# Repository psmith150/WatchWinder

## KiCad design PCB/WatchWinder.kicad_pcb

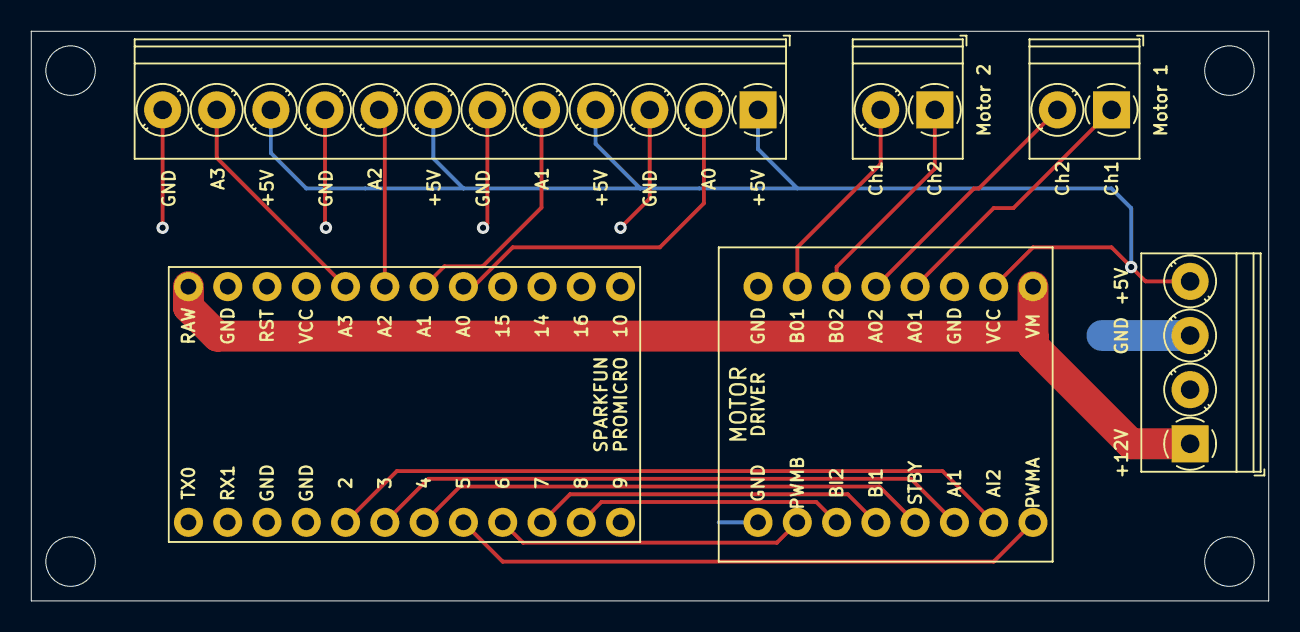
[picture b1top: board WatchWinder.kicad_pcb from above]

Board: 2 copper layers, 80.0 x 36.8 mm, 6 parts (0 on the bottom side), 18 nets.

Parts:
B1: SPARKFUN; SPARKFUN_PRO_MICRO
J1, J2: Screw_Terminal_01x02; TerminalBlock_Phoenix_PT-1,5-2-3.5-H_1x02_P3.50mm_Horizontal
J3: Screw_Terminal_01x12; TerminalBlock_Phoenix_PT-1,5-12-3.5-H_1x12_P3.50mm_Horizont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
J4: MOTOR; DRIVER
J5: Screw_Terminal_01x04; TerminalBlock_Phoenix_PT-1,5-4-3.5-H_1x04_P3.50mm_Horizontal

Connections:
+5V: J3.1, J3.4, J3.7, J3.10, J4.2, J5.4
+12V: B1.24, J4.1, J5.1
GND: B1.23, J3.3, J3.6, J3.9, J3.12, J4.16, J5.3
unnamed: B1.5, J4.10
unnamed: B1.6, J4.11
unnamed: B1.7, J4.12
unnamed: B1.8, J4.9
unnamed: B1.9, J4.15
unnamed: B1.10, J4.13
unnamed: B1.11, J4.14
unnamed: B1.17, J3.2
unnamed: B1.18, J3.5
unnamed: B1.19, J3.8
unnamed: B1.20, J3.11
unnamed: J1.1, J4.4
unnamed: J1.2, J4.5
unnamed: J2.1, J4.6
unnamed: J2.2, J4.7

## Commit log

2017-12-15 :lollipop: Added .gitattributes
2017-12-15 Project setup
    Added main file and motor driver library
2017-12-15 Sparkfun Board Def
    Added URL for Sparkfun board definitions.
2017-12-15 State Machine
    Outlined state machine for winder logic. Added excel table of winder
    parameter calculations.
2017-12-15 Updated documentation
    Added Pro Micro pinout and motor driver guide.
2017-12-16 Updated logic.
    Tested state machine logic. Added code for reading in analog inputs.
2020-12-04 Initial Creo CAD design
2020-12-05 Added bottom parts to FreeCad file
2020-12-06 Finished initial FreeCad conversion
2020-12-07 Added missing documentation. Updated sketch to use a next state. Created CAD for prototype winder holder
2020-12-20 Created PCB files. Removed Creo files.
2020-12-20 Added PCB project file
2020-12-20 Updated ground traces on PCB
2020-12-25 Created 3D print file
2020-12-25 V2 of watch pillow insert
